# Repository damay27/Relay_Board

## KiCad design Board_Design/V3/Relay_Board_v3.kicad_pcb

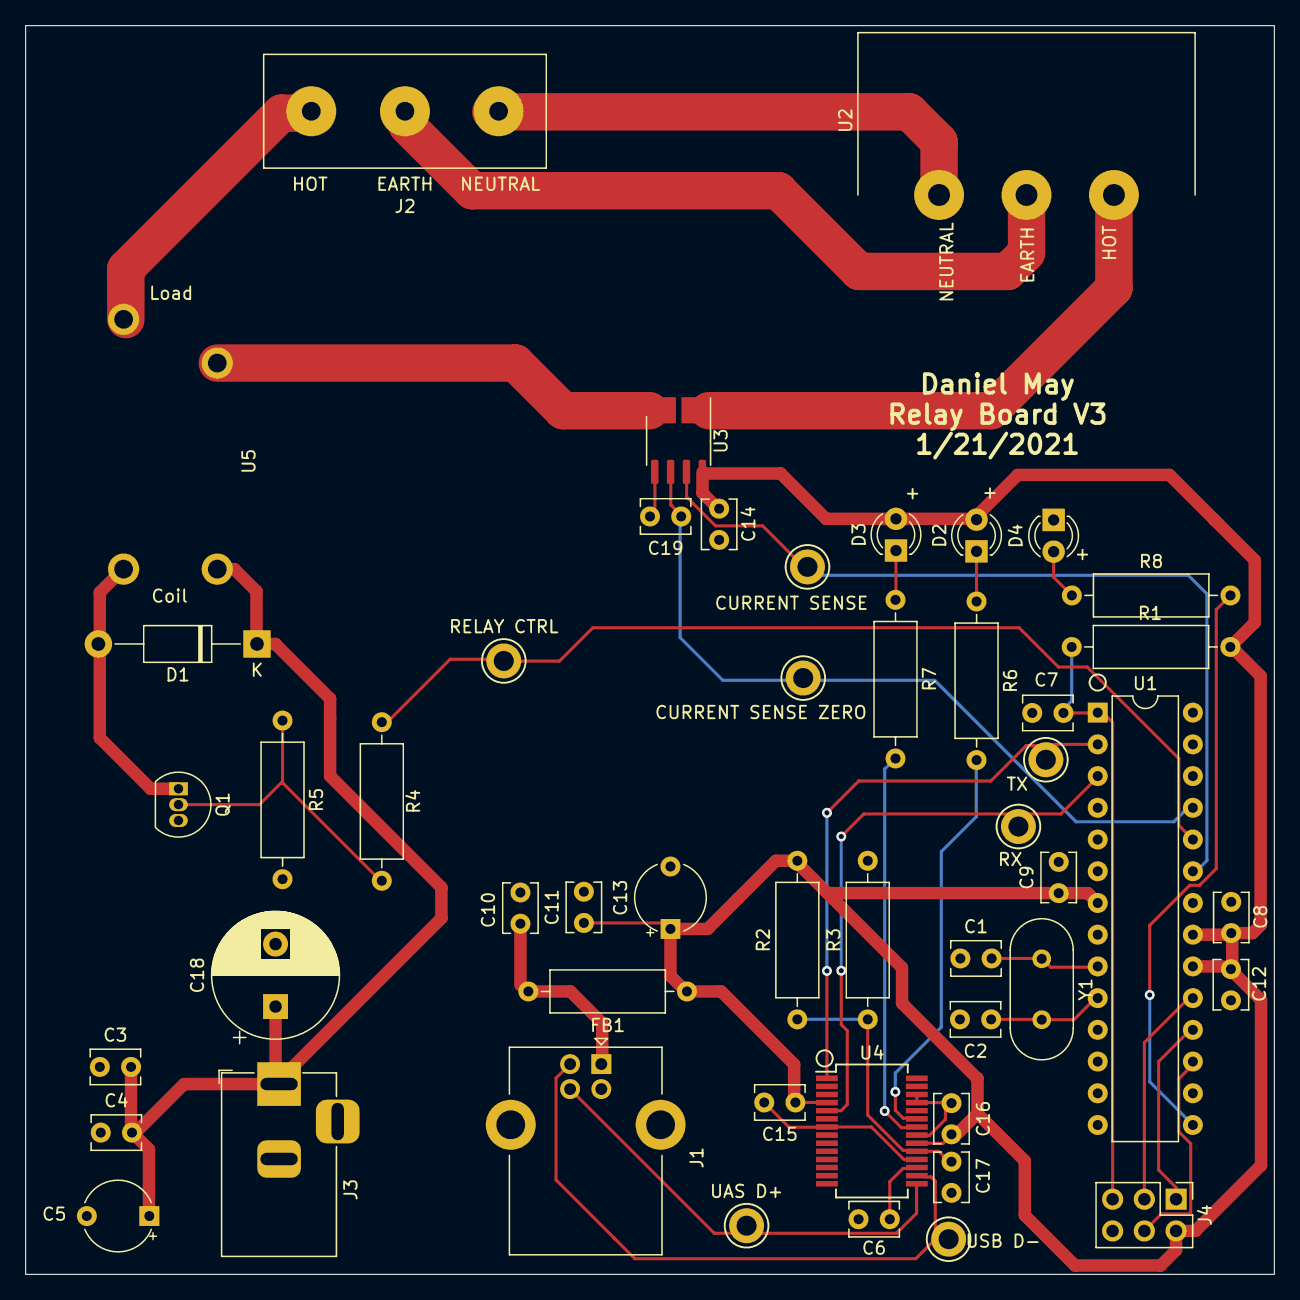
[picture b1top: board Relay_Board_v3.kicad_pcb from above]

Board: 2 copper layers, 100.0 x 100.0 mm, 50 parts (0 on the bottom side), 32 nets.

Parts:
C1, C2: 16pF; C_Disc_D3.8mm_W2.6mm_P2.50mm
C3, C10: 10nF; C_Disc_D3.8mm_W2.6mm_P2.50mm
C4, C6, C11: 100nF; C_Disc_D3.8mm_W2.6mm_P2.50mm
C5, C13: 4.7uF; CP_Radial_Tantal_D5.5mm_P5.00mm
C7, C8, C9, C12, C14, C15, C16, C17, C19: .1uF; C_Disc_D3.8mm_W2.6mm_P2.50mm
C18: 1000uF; CP_Radial_D10.0mm_P5.00mm
CURRENT SENSE: TestPoint_Keystone_5005-5009_Compact
CURRENT SENSE ZERO: TestPoint_Keystone_5005-5009_Compact
D1: D; D_DO-41_SOD81_P12.70mm_Horizontal
D2, D3, D4: LED; LED_D3.0mm
FB1: Ferrite_Bead; R_Axial_DIN0309_L9.0mm_D3.2mm_P12.70mm_Horizontal
J1: USB_B; USB_B_Lumberg_2411_02_Horizontal
J2: Screw_Terminal_01x03; Screw_Terminal_Pads
J3: Barrel_Jack_MountingPin; BarrelJack_Horizontal
J4: Conn_02x03_Odd_Even; PinHeader_2x03_P2.54mm_Vertical
Q1: BC337; TO-92_Inline
R1, R3: 10k; R_Axial_DIN0309_L9.0mm_D3.2mm_P12.70mm_Horizontal
R2: 4.7k; R_Axial_DIN0309_L9.0mm_D3.2mm_P12.70mm_Horizontal
R4, R6, R7: 220; R_Axial_DIN0309_L9.0mm_D3.2mm_P12.70mm_Horizontal
R5: 10K; R_Axial_DIN0309_L9.0mm_D3.2mm_P12.70mm_Horizontal
R8: 470; R_Axial_DIN0309_L9.0mm_D3.2mm_P12.70mm_Horizontal
RELAY CTRL: TestPoint_Keystone_5005-5009_Compact
RX: TestPoint_Keystone_5005-5009_Compact
TX: TestPoint_Keystone_5005-5009_Compact
U1: ATmega328P-PU; DIP-28_W7.62mm
U2: IEC_Connector
U3: ACS730xLCTR-20AB; SOIC-8_3.9x4.9mm_P1.27mm
U4: FT232RL; SSOP-28_5.3x10.2mm_P0.65mm
U5: G5PZ-1A-E_DC5
UAS D+: TestPoint_Keystone_5005-5009_Compact
USB D-: TestPoint_Keystone_5005-5009_Compact
Y1: 16MHz; Crystal_HC49-U_Vertical

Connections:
5V_Rail: C3.2, C4.2, C5.1, C18.1, D1.1, J3.1, U5.1
AC_Earth_IN: J2.1, U2.2
AC_Hot_IN: U2.0, U3.1, U3.2
AC_Hot_OUT: J2.3, U5.3
AC_Hot_Sense: U3.3, U3.4, U5.4
AC_Neutral_IN: J2.2, U2.1
Current_Sense: CURRENT SENSE.1, U1.23, U3.7
Current_Sense_Zero: C19.1, CURRENT SENSE ZERO.1, U1.25, U3.6
FTDI_UART_RX: RX.1, U1.3, U4.5
FTDI_UART_TX: TX.1, U1.2, U4.1
ISP_GND: C1.1, C2.2, C3.1, C4.1, C5.2, C6.1, C7.2, C8.2, C9.2, C10.1, C11.2, C12.1, C13.2, C14.2, C15.2, C16.1, C17.1, C18.2, C19.2, D4.1, J1.4, J1.5, J3.2, J4.6, Q1.3, R3.2, R5.2, U1.8, U1.22, U3.5, U4.7, U4.18, U4.21, U4.25, U4.26
ISP_MISO: J4.1, U1.18
ISP_MOSI: J4.4, U1.17
ISP_RST: C7.1, J4.5, R1.2, U1.1
ISP_SCK: J4.3, U1.19
unnamed: C6.2, U4.17
unnamed: C10.2, FB1.2, J1.1
unnamed: C17.2, R2.1, R3.1, U4.19
unnamed: D1.2, Q1.1, U5.2
unnamed: D2.1, R6.1
unnamed: D3.1, R7.1
unnamed: D4.2, R8.1
unnamed: Q1.2, R4.1, R5.1
unnamed: R6.2, U4.23
unnamed: R7.2, U4.22
unnamed: R8.2, U1.15
Relay_CTRL: R4.2, RELAY CTRL.1, U1.24
USB_D+: J1.3, U4.15, UAS D+.1
USB_D-: J1.2, U4.16, USB D-.1
USB_VBUS_Rail: C8.1, C9.1, C11.1, C12.2, C13.1, C14.1, C15.1, C16.2, D2.2, D3.2, FB1.1, J4.2, R1.1, R2.2, U1.7, U1.20, U1.21, U3.8, U4.4, U4.20
XTAL1: C1.2, U1.9, Y1.1
XTAL2: C2.1, U1.10, Y1.2

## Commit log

2021-06-30 Added 4th revision of the board with the USB data traces differentially routed.
